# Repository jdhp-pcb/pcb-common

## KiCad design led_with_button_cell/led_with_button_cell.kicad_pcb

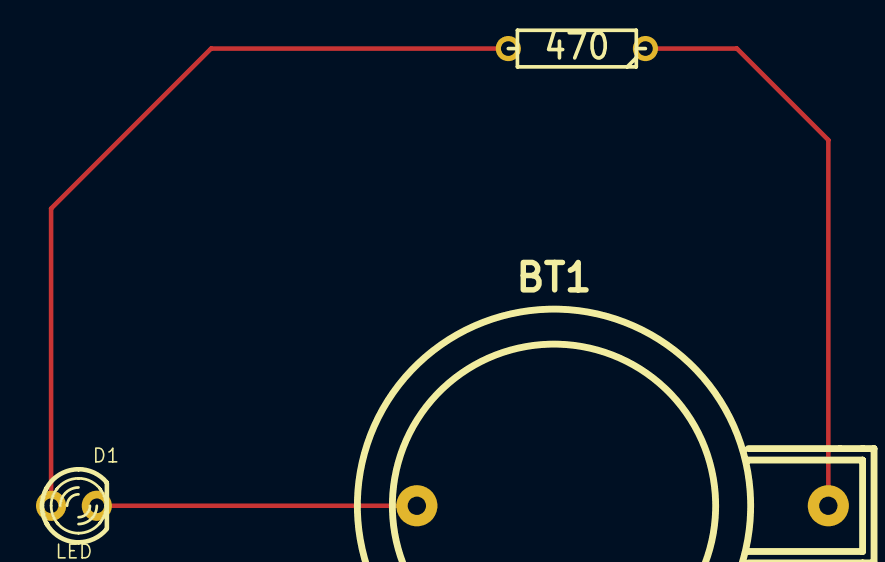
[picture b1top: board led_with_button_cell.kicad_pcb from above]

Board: 2 copper layers, 3 parts (0 on the bottom side), 3 nets.

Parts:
BT1: BATTERY; CR2032H
D1: LED; LED-3MM
R1: 470; R3

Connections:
+BATT: BT1.1, R1.1
GND: BT1.2, D1.2
unnamed: D1.1, R1.2

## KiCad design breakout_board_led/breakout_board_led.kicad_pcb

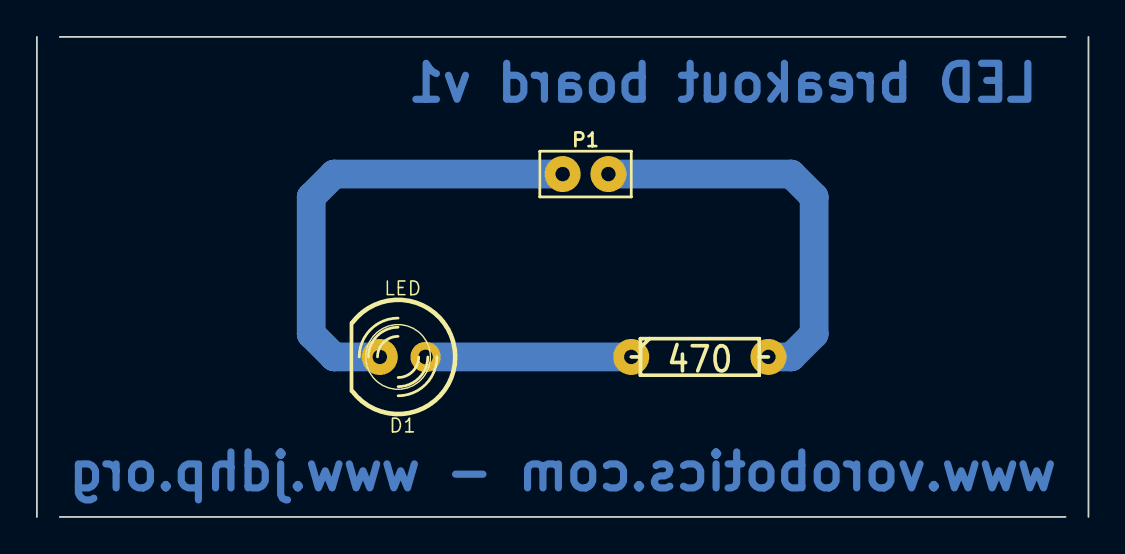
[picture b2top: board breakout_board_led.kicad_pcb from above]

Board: 2 copper layers, 58.4 x 26.7 mm, 3 parts (0 on the bottom side), 3 nets.

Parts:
D1: LED; LED-5MM
P1: CONN_2; PIN_ARRAY_2X1
R1: 470; R3

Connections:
unnamed: D1.1, R1.1
unnamed: D1.2, P1.1
unnamed: P1.2, R1.2

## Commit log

2014-10-14 Add 'breakout_board_led' PCB.
2014-10-14 Add 'avr_programmer' PCB.
2014-10-14 Add '.gitignore'.
2014-10-14 Add 'led_with_button_cell' PCB.
2014-10-14 Add 'test_track_width' PCB.
2014-10-19 Update 'avr_programmer'.
